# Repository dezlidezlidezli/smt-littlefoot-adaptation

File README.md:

# smt-littlefoot-adaptation
A version of the littlefoot keyboard by The Royal with an integrated MCU, rather than being based on a pro-micro board. Untested, and not compatible with existing cases. case design soontm

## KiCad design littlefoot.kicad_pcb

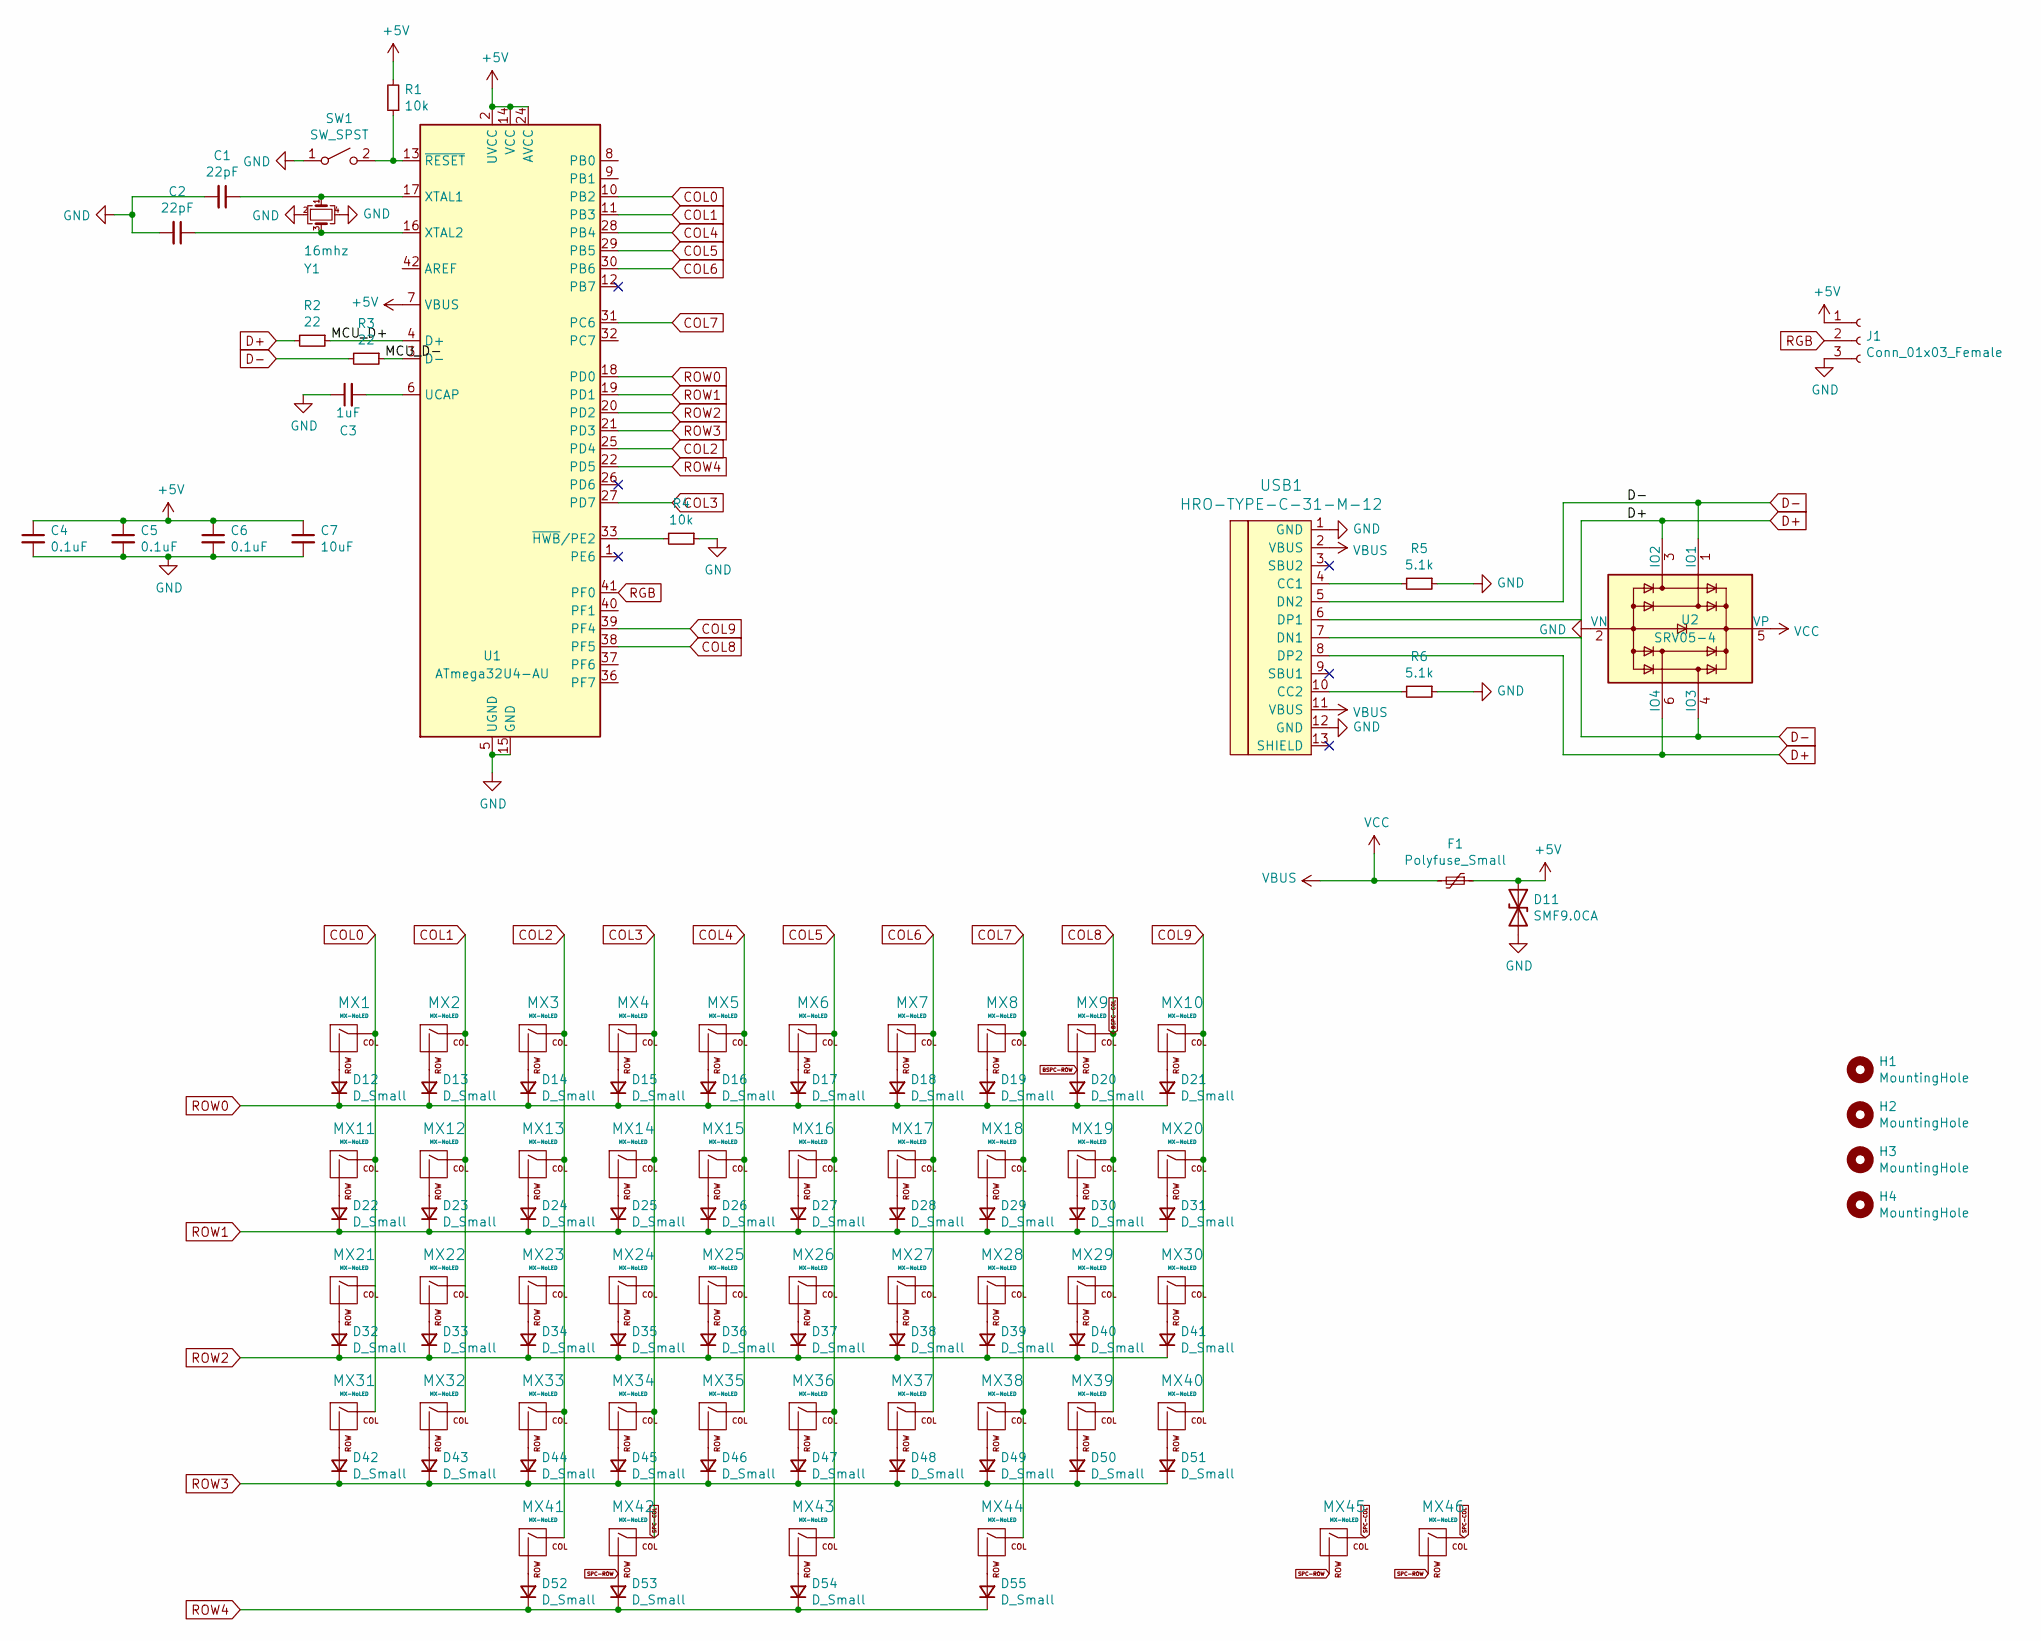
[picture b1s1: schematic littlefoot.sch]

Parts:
C1, C2: 22pF; C_0603_1608Metric
C3: 1uF; C_0603_1608Metric
C4, C5, C6: 0.1uF; C_0603_1608Metric
C7: 10uF; C_0603_1608Metric
D11: SMF9.0CA; D_SOD-123
D12, D13, D14, D15, D16, D17, D18, D19, D20, D21, D22, D23, D24, D25, D26, D27, D28, D29, D30, D31, D32, D33, D34, D35, D36, D37, D38, D39, D40, D41, D42, D43, D44, D45, D46, D47, D48, D49, D50, D51, D52, D53, D54, D55: D_Small; D_SOD-123
F1: Polyfuse_Small; Fuse_1206_3216Metric
H1, H2, H3, H4: MountingHole; MountingHole_4.3mm_M4_Pad
J1: Conn_01x03_Female; PinHeader_1x03_P2.54mm_Vertical
MX1, MX2, MX3, MX4, MX5, MX6, MX7, MX8, MX9, MX10, MX11, MX12, MX13, MX14, MX15, MX16, MX17, MX18, MX19, MX20, MX21, MX22, MX23, MX24, MX25, MX26, MX27, MX28, MX29, MX30, MX31, MX32, MX33, MX34, MX35, MX36, MX37, MX38, MX39, MX40: MX-NoLED; MX-ALPS_1u_NoLED
MX41, MX44: MX-NoLED; MX-ALPS_1.5u_NoLED
MX42, MX43: MX-NoLED; MX-ALPS_2u_ReversedStabilizers_NoLED
MX45: MX-NoLED; MX-ALPS_7u_ReversedStabilizers_NoLED
MX46: MX-NoLED; MX-ALPS_8u_ReversedStabilizers_NoLED
R1, R4: 10k; R_0603_1608Metric
R2, R3: 22; R_0603_1608Metric
R5, R6: 5.1k; R_0603_1608Metric
SW1: SW_SPST; SW_SPST_TL3342
U1: ATmega32U4-AU; TQFP-44_10x10mm_Pitch0.8mm
U2: SRV05-4; SOT-23-6
USB1: HRO-TYPE-C-31-M-12; HRO-TYPE-C-31-M-12-HandSoldering
Y1: 16mhz; Crystal_SMD_3225-4Pin_3.2x2.5mm

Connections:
+5V: C4.1, C5.1, C6.1, C7.1, D11.1 (A1), F1.1, J1.1, R1.2, U1.2 (UVCC), U1.7 (VBUS), U1.14 (VCC), U1.24 (AVCC), U1.34 (VCC), U1.44 (AVCC)
/MCU_D+: R2.1, U1.4 (D+)
/MCU_D-: R3.1, U1.3 (D-)
BSPC-COL: MX9.1 (COL), MX19.1 (COL), MX29.1 (COL), MX39.1 (COL), U1.38 (PF5)
BSPC-ROW: D20.2 (A), MX9.2 (ROW)
COL0: MX1.1 (COL), MX11.1 (COL), MX21.1 (COL), MX31.1 (COL), U1.10 (PB2)
COL1: MX2.1 (COL), MX12.1 (COL), MX22.1 (COL), MX32.1 (COL), U1.11 (PB3)
COL2: MX3.1 (COL), MX13.1 (COL), MX23.1 (COL), MX33.1 (COL), MX41.1 (COL), U1.25 (PD4)
COL3: MX4.1 (COL), MX14.1 (COL), MX24.1 (COL), MX34.1 (COL), MX42.1 (COL), MX45.1 (COL), MX46.1 (COL), U1.27 (PD7)
COL4: MX5.1 (COL), MX15.1 (COL), MX25.1 (COL), MX35.1 (COL), U1.28 (PB4)
COL5: MX6.1 (COL), MX16.1 (COL), MX26.1 (COL), MX36.1 (COL), MX43.1 (COL), U1.29 (PB5)
COL6: MX7.1 (COL), MX17.1 (COL), MX27.1 (COL), MX37.1 (COL), U1.30 (PB6)
COL7: MX8.1 (COL), MX18.1 (COL), MX28.1 (COL), MX38.1 (COL), MX44.1 (COL), U1.31 (PC6)
COL9: MX10.1 (COL), MX20.1 (COL), MX30.1 (COL), MX40.1 (COL), U1.39 (PF4)
D+: R2.2, U2.3 (IO2), U2.6 (IO4), USB1.6 (DP1), USB1.8 (DP2)
D-: R3.2, U2.1 (IO1), U2.4 (IO3), USB1.5 (DN2), USB1.7 (DN1)
GND: C1.2, C2.2, C3.1, C4.2, C5.2, C6.2, C7.2, D11.2 (A2), J1.3, R4.1, R5.1, R6.1, SW1.1 (A), U1.5 (UGND), U1.15 (GND), U1.23 (GND), U1.35 (GND), U1.43 (GND), U2.2 (VN), USB1.1 (GND), USB1.12 (GND), Y1.2, Y1.4
unnamed: C1.1, U1.17 (XTAL1), Y1.1
unnamed: C2.1, U1.16 (XTAL2), Y1.3
unnamed: C3.2, U1.6 (UCAP)
unnamed: D12.2 (A), MX1.2 (ROW)
unnamed: D13.2 (A), MX2.2 (ROW)
unnamed: D14.2 (A), MX3.2 (ROW)
unnamed: D15.2 (A), MX4.2 (ROW)
unnamed: D16.2 (A), MX5.2 (ROW)
unnamed: D17.2 (A), MX6.2 (ROW)
unnamed: D18.2 (A), MX7.2 (ROW)
unnamed: D19.2 (A), MX8.2 (ROW)
unnamed: D21.2 (A), MX10.2 (ROW)
unnamed: D22.2 (A), MX11.2 (ROW)
unnamed: D23.2 (A), MX12.2 (ROW)
unnamed: D24.2 (A), MX13.2 (ROW)
unnamed: D25.2 (A), MX14.2 (ROW)
unnamed: D26.2 (A), MX15.2 (ROW)
unnamed: D27.2 (A), MX16.2 (ROW)
unnamed: D28.2 (A), MX17.2 (ROW)
unnamed: D29.2 (A), MX18.2 (ROW)
unnamed: D30.2 (A), MX19.2 (ROW)
unnamed: D31.2 (A), MX20.2 (ROW)
unnamed: D32.2 (A), MX21.2 (ROW)
unnamed: D33.2 (A), MX22.2 (ROW)
unnamed: D34.2 (A), MX23.2 (ROW)
unnamed: D35.2 (A), MX24.2 (ROW)
unnamed: D36.2 (A), MX25.2 (ROW)
unnamed: D37.2 (A), MX26.2 (ROW)
unnamed: D38.2 (A), MX27.2 (ROW)
unnamed: D39.2 (A), MX28.2 (ROW)
unnamed: D40.2 (A), MX29.2 (ROW)
unnamed: D41.2 (A), MX30.2 (ROW)
unnamed: D42.2 (A), MX31.2 (ROW)
unnamed: D43.2 (A), MX32.2 (ROW)
unnamed: D44.2 (A), MX33.2 (ROW)
unnamed: D45.2 (A), MX34.2 (ROW)
unnamed: D46.2 (A), MX35.2 (ROW)
unnamed: D47.2 (A), MX36.2 (ROW)
unnamed: D48.2 (A), MX37.2 (ROW)
unnamed: D49.2 (A), MX38.2 (ROW)
unnamed: D50.2 (A), MX39.2 (ROW)
unnamed: D51.2 (A), MX40.2 (ROW)
unnamed: D52.2 (A), MX41.2 (ROW)
unnamed: D54.2 (A), MX43.2 (ROW)
unnamed: D55.2 (A), MX44.2 (ROW)
unnamed: R1.1, SW1.2 (B), U1.13 (~RESET)
unnamed: R4.2, U1.33 (~HWB~/PE2)
unnamed: R5.2, USB1.4 (CC1)
unnamed: R6.2, USB1.10 (CC2)
RGB: J1.2, U1.41 (PF0)
ROW0: D12.1 (K), D13.1 (K), D14.1 (K), D15.1 (K), D16.1 (K), D17.1 (K), D18.1 (K), D19.1 (K), D20.1 (K), D21.1 (K), U1.18 (PD0)
ROW1: D22.1 (K), D23.1 (K), D24.1 (K), D25.1 (K), D26.1 (K), D27.1 (K), D28.1 (K), D29.1 (K), D30.1 (K), D31.1 (K), U1.19 (PD1)
ROW2: D32.1 (K), D33.1 (K), D34.1 (K), D35.1 (K), D36.1 (K), D37.1 (K), D38.1 (K), D39.1 (K), D40.1 (K), D41.1 (K), U1.20 (PD2)
ROW3: D42.1 (K), D43.1 (K), D44.1 (K), D45.1 (K), D46.1 (K), D47.1 (K), D48.1 (K), D49.1 (K), D50.1 (K), D51.1 (K), U1.21 (PD3)
ROW4: D52.1 (K), D53.1 (K), D54.1 (K), D55.1 (K), U1.22 (PD5)
SPC-ROW: D53.2 (A), MX42.2 (ROW), MX45.2 (ROW), MX46.2 (ROW)
VBUS: F1.2, U2.5 (VP), USB1.2 (VBUS), USB1.11 (VBUS)

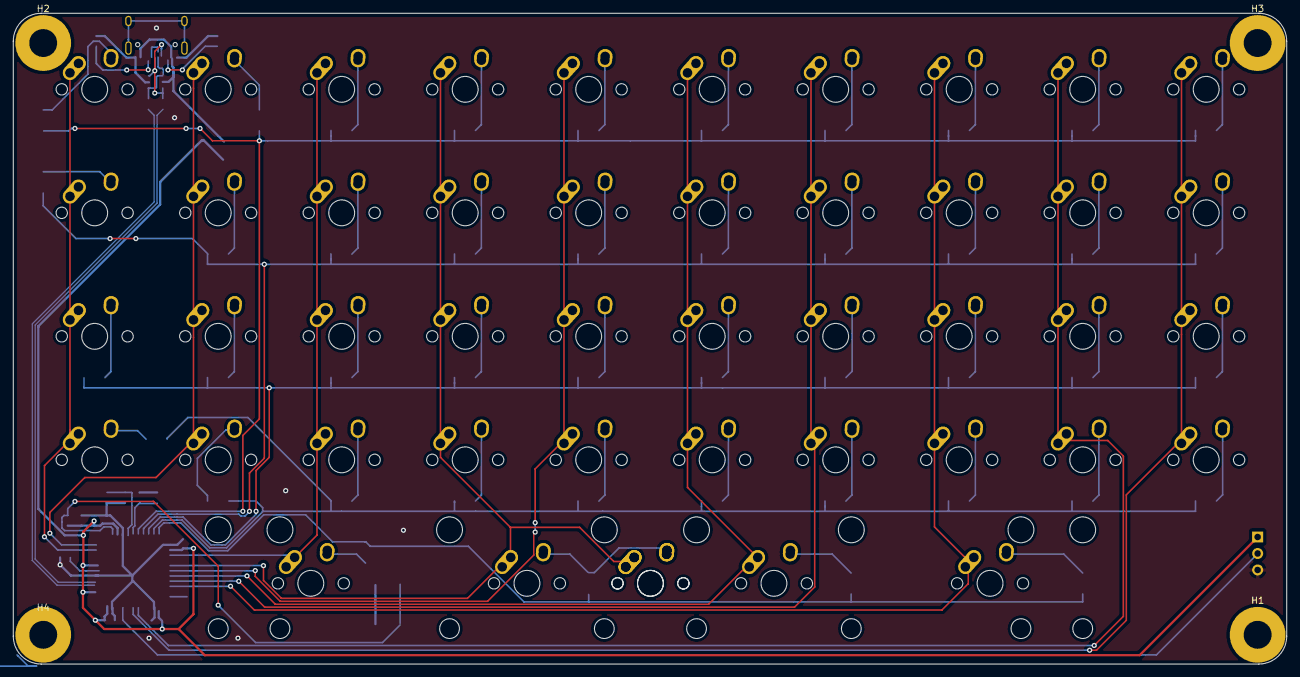
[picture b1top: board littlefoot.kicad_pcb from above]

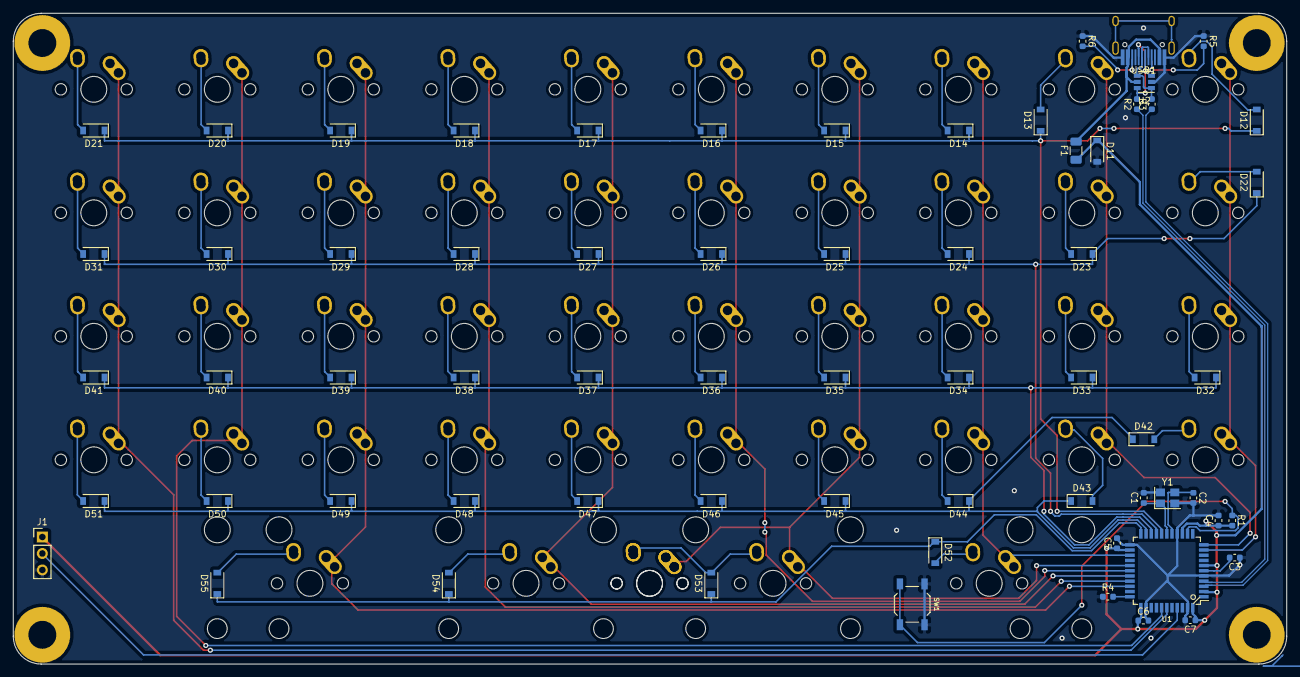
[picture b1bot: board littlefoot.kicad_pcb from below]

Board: 2 copper layers, 196.4 x 100.4 mm, 115 parts (65 on the bottom side), 74 nets.

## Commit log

2020-12-09 commit final?
